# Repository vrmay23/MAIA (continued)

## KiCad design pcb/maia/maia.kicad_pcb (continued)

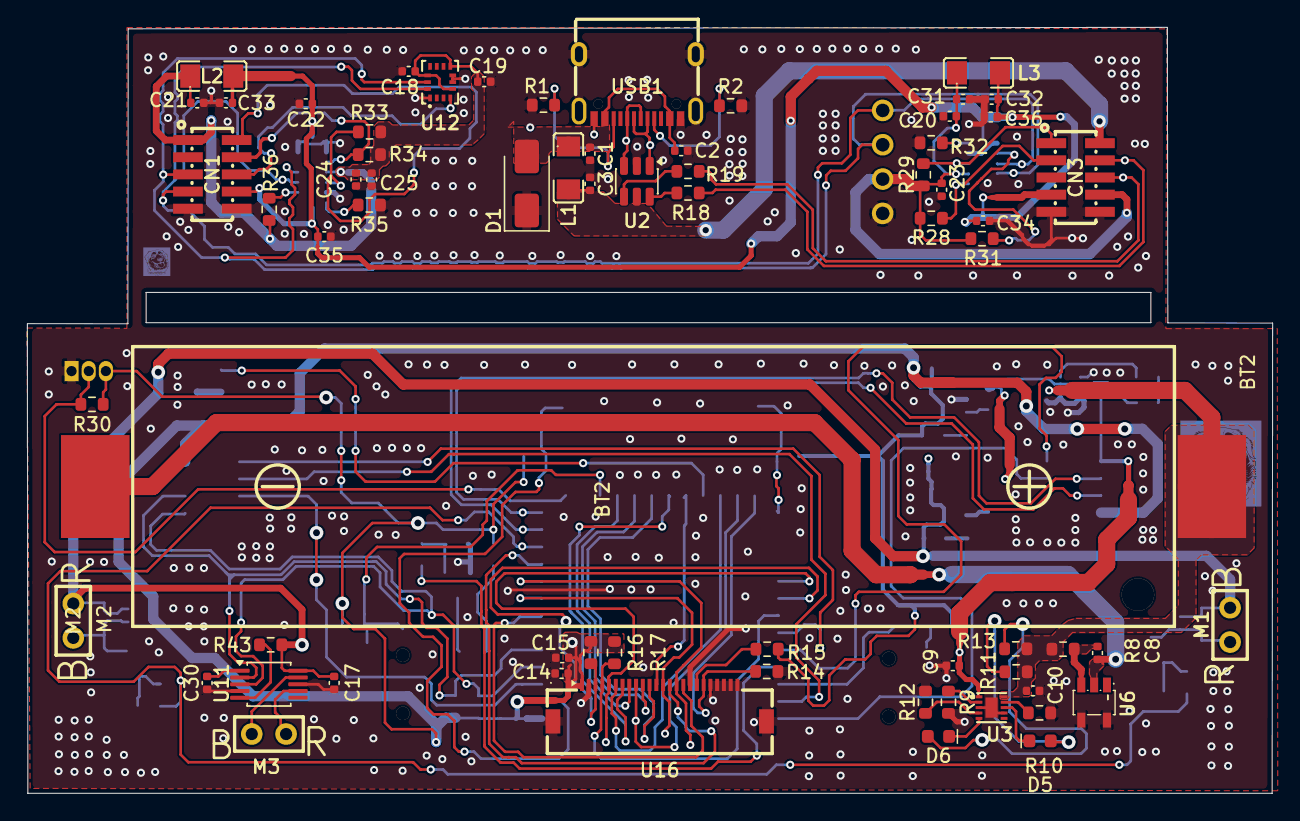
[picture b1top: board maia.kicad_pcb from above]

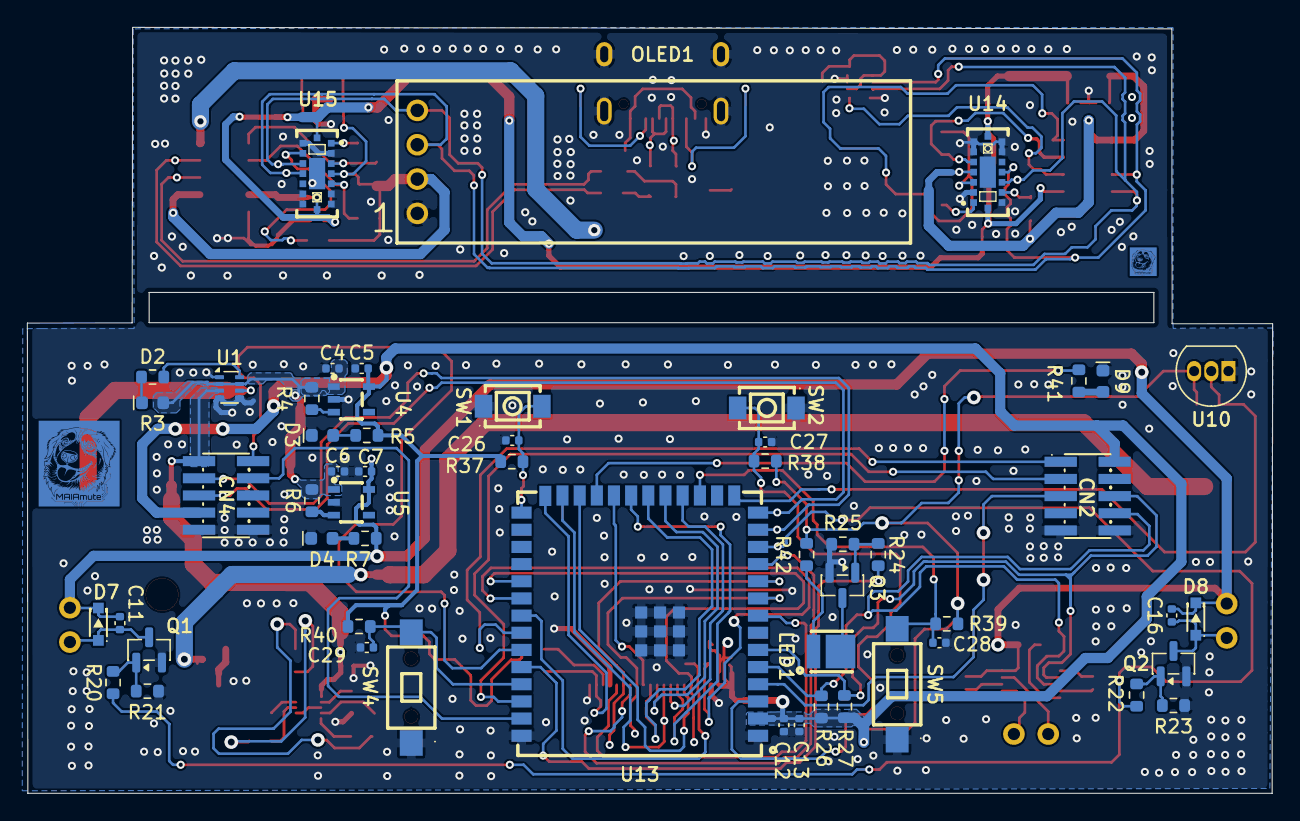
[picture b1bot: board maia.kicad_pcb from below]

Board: 4 copper layers, 92.1 x 56.7 mm, 122 parts (55 on the bottom side), 78 nets.

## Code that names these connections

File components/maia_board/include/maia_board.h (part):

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    *      1    |   -    | GND                |
    *      2    |   -    | 3v3_esp            | 3V3 supply
    *      3    |   -    | enable_esp         | EN / reset
    *      4    | GPIO04 | MPU_int            | IMU interrupt
    *      5    | GPIO05 | I2C_SDA            | I2C bus SDA
    *      6    | GPIO06 | I2C_SCL            | I2C bus SCL
    *      7    | GPIO07 | Motor_Left_PWM     | Left ERM motor PWM
    *      8    | GPIO15 | CAM_Y2             | Camera data
    *      9    | GPIO16 | CAM_Y5             | Camera data
    *     10    | GPIO17 | CAM_Y3             | Camera data
    *     11    | GPIO18 | CAM_Y4             | Camera data
    *     12    | GPIO08 | Motor_Right_PWM    | Right ERM motor PWM
    *     13    | GPIO19 | usb_N              | Native USB D-
    *     14    | GPIO20 | usb_P              | Native USB D+
    *     15    | GPIO03 | DS18B20_DATA       | OneWire data
    *     16    | GPIO46 | -                  | Not connected (DNU)
    *     17    | GPIO09 | BTN_01             | Button 1
    *     18    | GPIO10 | CAM_XCLK           | Camera clock in
    *     19    | GPIO11 | CAM_Y8             | Camera data
    *     20    | GPIO12 | CAM_Y7             | Camera data
    *     21    | GPIO13 | CAM_PCLK           | Camera pixel clock
    *     22    | GPIO14 | CAM_PWDN           | Camera power down
    *     23    | GPIO21 | CAM_Y9             | Camera data
    *     24    | GPIO47 | CAM_HREF           | Camera HREF
    *     25    | GPIO48 | USER_LED           | User / status LED
    *     26    | GPIO45 | CAM_Y6             | Camera data
    *     27    | GPIO00 | boot_esp           | Boot strapping pin
    *     28    | GPIO35 | -                  | Not connected (DNU)
    *     29    | GPIO36 | -                  | Not connected (DNU)
    *     30    | GPIO37 | -                  | Not connected (DNU)
    *     31    | GPIO38 | CAM_VSYNC          | Camera VSYNC
    *     32    | GPIO39 | SCCB_SCL           | Camera SCCB clock
    *     33    | GPIO40 | SCCB_SDA           | Camera SCCB data
    *     34    | GPIO41 | VL53L5CX_INT_RIGHT | ToF right INT
    *     35    | GPIO42 | VL53L5CX_INT_LEFT  | ToF left INT
    *     36    | GPIO44 | LED_FLASH          | Camera flash LED  (U0RXD)
    *     37    | GPIO43 | BTN_02             | Button 2          (U0TXD)
    *     38    | GPIO02 | VL53L5CX_LP_RIGHT  | ToF right LPn
    *     39    | GPIO01 | VL53L5CX_LP_LEFT   | ToF left LPn
    *     40    |   -    | GND                |
    *     41    |   -    | GND                |
    *  ------------------------------------------------------------------
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
    /* Buttons */

    #define MAIA_GPIO_BUTTON            9      /* BTN_01                   */
    #define MAIA_GPIO_BUTTON_2          43     /* BTN_02 (U0TXD)           */

    /* LEDs */

    #define MAIA_GPIO_LED_USER          48     /* USER_LED                 */
    #define MAIA_GPIO_LED_FLASH         44     /* LED_FLASH (U0RXD)        */
    #define MAIA_GPIO_LED_STATUS        CONFIG_MAIA_LED_STATUS_PIN

    /* Camera (OV2640) - no driver yet, pinout for reference */
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
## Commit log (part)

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2026-01-07 It was added the disclaimer on the README.md
2026-01-08 Basic configuration and arquitecture have been defined. We can compile the code and flash the hello_world.
2026-01-08 It was add the support to the MAIA_BOARD via Menuconfig.
2026-01-10 feat(maia_board): add comprehensive Kconfig and LED support
    - Created complete Kconfig menu structure with 46 configuration symbols
    - Added General Configuration (timeouts, software version, animal/tutor info)
    - Added Radio Configuration (WiFi AP/STA modes, button triggers)
    - Added GPIO Configuration (PWM motors, button, LED status)
    - Added Bus Configuration (I2C frequency, device enables/addresses)
    - Implemented maia_config.c for startup configuration logging
2026-01-11 feat(button): implement complete button driver with state machine
    - Add button driver with debouncing and event detection
    - Support 7 event types: PRESSED, RELEASED, SINGLE_CLICK, DOUBLE_CLICK,
    LONG_PRESS, EXTRA_LONG_PRESS_1, EXTRA_LONG_PRESS_2
    - Implement cascading ESP timers for efficient threshold detection
    - Add Kconfig menu for all timing parameters
    - Create test framework with LED feedback
2026-01-11 feat(drivers): implement DS18B20 OneWire temperature sensor driver
    - Add complete OneWire protocol implementation in maia_onewire.c
    * Reset pulse detection with presence check
    * Bit-level read/write operations (LSB first)
    * Byte-level read/write operations
    * Dallas/Maxim CRC8 checksum calculation
    * Precise timing using esp_rom_delay_us()
2026-01-18 driver drv2605l was implemented with test functions
2026-02-09 SSD1306 has been implemented but need some adjustments in the 4th row and separete the fonts in a new file.
2026-03-22 feat(mpu6050): add MPU-6050 IMU driver and test suite
    - New driver: components/drivers/mpu6050/ (init, raw/scaled reads,
    calibration, self-test, sleep/wake, range config, DMP skeleton)
    - New test: main/tests/test_mpu6050.c (8 Phase 1 tests, all PASS)
    - Fix: memset i2c_device_config_t before add_device — ESP-IDF v6.0
    internal fields (flags, scl_wait_us) must be zero, stack garbage
    caused ESP_ERR_INVALID_STATE on first transmit
2026-04-05 Update README with dependencies and building instructions
    Added detailed information about third-party dependencies, integration approach, and building instructions. Updated the disclaimer section for clarity.
2026-04-06 feat(vl53l5cx): add ToF driver v0.6.0 with platform layer, Kconfig and tests
    - Add platform.h: MAIA VL53L5CX_Platform with ESP-IDF v6.0 I2C master API
    - Add vl53l5cx_platform.c: WrByte/WrMulti/RdByte/RdMulti/WaitMs/SwapBuffer
    - Add vl53l5cx.c/h: dual sensor driver with LPn address reassignment
    - Add test_vl53l5cx.c: Phase 1 test suite (8 tests)
    - Update Kconfig: 9 new VL53L5CX params + MAIA_TEST_TOF
    - Update drivers/CMakeLists.txt: include ULD sources from managed_components
2026-04-06 feat: add VL53L5CX driver skeleton and platform layer
2026-06-19 It was add the pcb rev0 and the spec/doc rev5
